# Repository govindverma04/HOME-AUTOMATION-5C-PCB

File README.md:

# HOME-AUTOMATION-5C-PCB

# Smart Home Automation PCB

This is an open-source ESP32-based smart home automation PCB designed by me.  
It includes zero-cross detection, triac dimming, relay control and support for Alexa/Google integration (optional).

---

## 🚀 Features
- ESP32-based main controller  
- 4N25 Zero-Cross Detection  
- Triac-based AC dimming  
- Relay output for AC load ON/OFF  
- Indicator LEDs  
- Safe opto-isolated design  
- Can be used for fan dimming & bulb control  

---

## 🧰 Files in this Repository
- `schematics/` → Circuit diagram  
- `pcb/` → PCB design files  
- `firmware/` → ESP32 code  
- `bom/` → Part list of components  
- `images/` → PCB photos & renders  

---

## 🔧 How to Use / Instructions

### 1) Assemble the PCB
- Solder all resistors  
- Solder optocouplers (4N25, MOC3021, etc)  
- Solder triac (BT136 or chosen model)  
- Mount terminal blocks  
- Insert ESP32  

### 2) Power Requirements
- 5V input via Hi-Link / External SMPS  
- ESP32 runs at 3.3V (regulator included)

### 3) Upload the Firmware
1. Download code from `firmware/` folder  
2. Open in Arduino IDE or PlatformIO  
3. Select board → ESP32 Dev Module  
4. Upload code  
5. Open Serial Monitor → you should see boot messages  

### 4) Connecting AC Load (⚠️ Safety First!)
- Only connect AC when you are confident  
- Use proper insulation  
- Fan/Bulb should connect through triac output  
- Relay output supports ON/OFF loads  

---

## 🧪 Testing
- Connect a test load or bulb  
- Verify Zero-Cross is detected (LED should blink)  
- Check dimming using serial or app  
- Test safety circuits  

---

## 🤝 Contributing
If you want to improve this project:
- Open an issue  
- Submit a pull request  
- Suggest new features  

---

## 📜 License
This project is open-source under the MIT License.

---

## 📞 Contact
Maintainer: **Govind**  
GitHub: https://github.com/govindverma04

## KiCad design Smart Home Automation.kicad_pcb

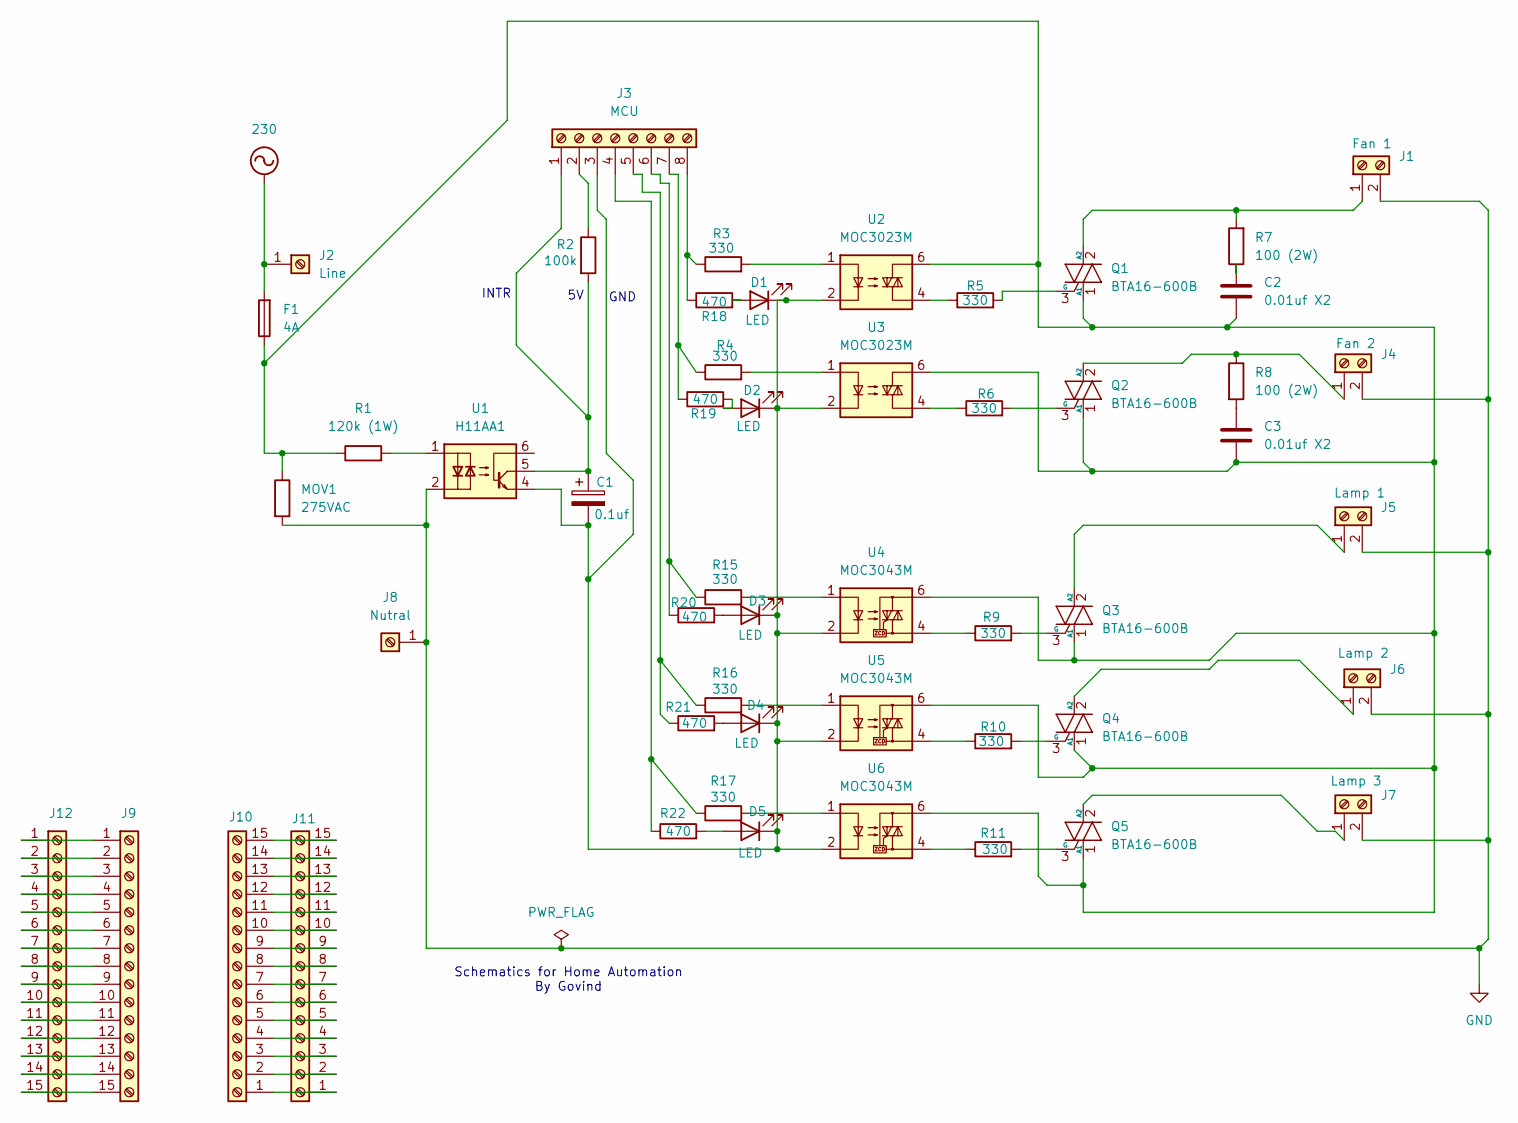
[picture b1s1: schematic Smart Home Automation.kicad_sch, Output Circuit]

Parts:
C1: 0.1uf; CP_Radial_D5.0mm_P2.00mm
C2, C3: 0.01uf X2; CP_Radial_D5.0mm_P2.00mm
D1, D2, D3, D4, D5: LED; LED_D1.8mm_W3.3mm_H2.4mm
F1: 4A; Fuseholder_Cylinder-5x20mm_Schurter_0031_8201_Horizontal_Op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
J1: Fan 1; PinSocket_1x02_P2.54mm_Vertical
J2: Line; Pin_D0.7mm_L6.5mm_W1.8mm_FlatFork
J3: MCU; PinSocket_1x08_P2.54mm_Vertical
J4: Fan 2; PinSocket_1x02_P2.54mm_Vertical
J5: Lamp 1; PinSocket_1x02_P2.54mm_Vertical
J6: Lamp 2; PinSocket_1x02_P2.54mm_Vertical
J7: Lamp 3; PinSocket_1x02_P2.54mm_Vertical
J8: Nutral; Pin_D0.7mm_L6.5mm_W1.8mm_FlatFork
J9, J10, J11, J12: Screw_Terminal_01x15; PinSocket_1x15_P2.54mm_Vertical
MOV1: 275VAC; RV_Disc_D7mm_W3.4mm_P5mm
Q1, Q2, Q3, Q4, Q5: BTA16-600B; TO-220-3_Vertical
R1: 120k (1W); R_Axial_DIN0204_L3.6mm_D1.6mm_P7.62mm_Horizontal
R2: 100k; R_Axial_DIN0204_L3.6mm_D1.6mm_P5.08mm_Horizontal
R3, R4, R5, R6, R9, R10, R11, R15, R16, R17: 330; R_Axial_DIN0204_L3.6mm_D1.6mm_P5.08mm_Horizontal
R7, R8: 100 (2W); R_Axial_DIN0204_L3.6mm_D1.6mm_P5.08mm_Horizontal
R18, R19, R20, R21, R22: 470; R_Axial_DIN0204_L3.6mm_D1.6mm_P5.08mm_Horizontal
U1: H11AA1; DIP-6_W7.62mm
U2, U3: MOC3023M; DIP-6_W10.16mm
U4, U5, U6: MOC3043M; DIP-6_W10.16mm

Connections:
230: F1.2, J2.1
GND: J1.2, J4.2, J5.2, J6.2, J7.2, J8.1, MOV1.2, U1.2
unnamed: C2.1, R7.1
unnamed: C3.1, R8.2
unnamed: D1.2 (A), R18.2
unnamed: C1.2, D1.1 (K), D2.1 (K), D3.1 (K), D4.1 (K), D5.1 (K), J3.3, U1.4, U2.2, U3.2, U4.2, U5.2, U6.2
unnamed: D2.2 (A), R19.2
unnamed: D3.2 (A), R20.2
unnamed: D4.2 (A), R21.2
unnamed: D5.2 (A), R22.2
unnamed: J1.1, Q1.2 (A2), R7.2
unnamed: C1.1, J3.1, R2.2, U1.5
unnamed: J3.2, R2.1
unnamed: J3.4, R17.1, R22.1
unnamed: J3.5, R16.1, R21.1
unnamed: J3.6, R15.1, R20.1
unnamed: J3.7, R4.1, R19.1
unnamed: J3.8, R3.1, R18.1
unnamed: J4.1, Q2.2 (A2), R8.1
unnamed: J5.1, Q3.2 (A2)
unnamed: J6.1, Q4.2 (A2)
unnamed: J7.1, Q5.2 (A2)
unnamed: J10.1, J11.1
unnamed: J10.2, J11.2
unnamed: J10.3, J11.3
unnamed: J10.4, J11.4
unnamed: J10.5, J11.5
unnamed: J10.6, J11.6
unnamed: J10.7, J11.7
unnamed: J10.8, J11.8
unnamed: J10.9, J11.9
unnamed: J10.10, J11.10
unnamed: J10.11, J11.11
unnamed: J10.12, J11.12
unnamed: J10.13, J11.13
unnamed: J10.14, J11.14
unnamed: J10.15, J11.15
unnamed: J9.1, J12.1
unnamed: J9.2, J12.2
unnamed: J9.3, J12.3
unnamed: J9.4, J12.4
unnamed: J9.5, J12.5
unnamed: J9.6, J12.6
unnamed: J9.7, J12.7
unnamed: J9.8, J12.8
unnamed: J9.9, J12.9
unnamed: J9.10, J12.10
unnamed: J9.11, J12.11
unnamed: J9.12, J12.12
unnamed: J9.13, J12.13
unnamed: J9.14, J12.14
unnamed: J9.15, J12.15
unnamed: C2.2, C3.2, F1.1, MOV1.1, Q1.1 (A1), Q2.1 (A1), Q3.1 (A1), Q4.1 (A1), Q5.1 (A1), R1.1, U2.6, U3.6, U4.6, U5.6, U6.6
unnamed: Q1.3 (G), R5.2
unnamed: Q2.3 (G), R6.2
unnamed: Q3.3 (G), R9.2
unnamed: Q4.3 (G), R10.2
unnamed: Q5.3 (G), R11.2
unnamed: R1.2, U1.1
unnamed: R3.2, U2.1
unnamed: R4.2, U3.1
unnamed: R5.1, U2.4
unnamed: R6.1, U3.4
unnamed: R9.1, U4.4
unnamed: R10.1, U5.4
unnamed: R11.1, U6.4
unnamed: R15.2, U4.1
unnamed: R16.2, U5.1
unnamed: R17.2, U6.1

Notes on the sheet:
Schematics for Home Automation By Govind
INTR
GND

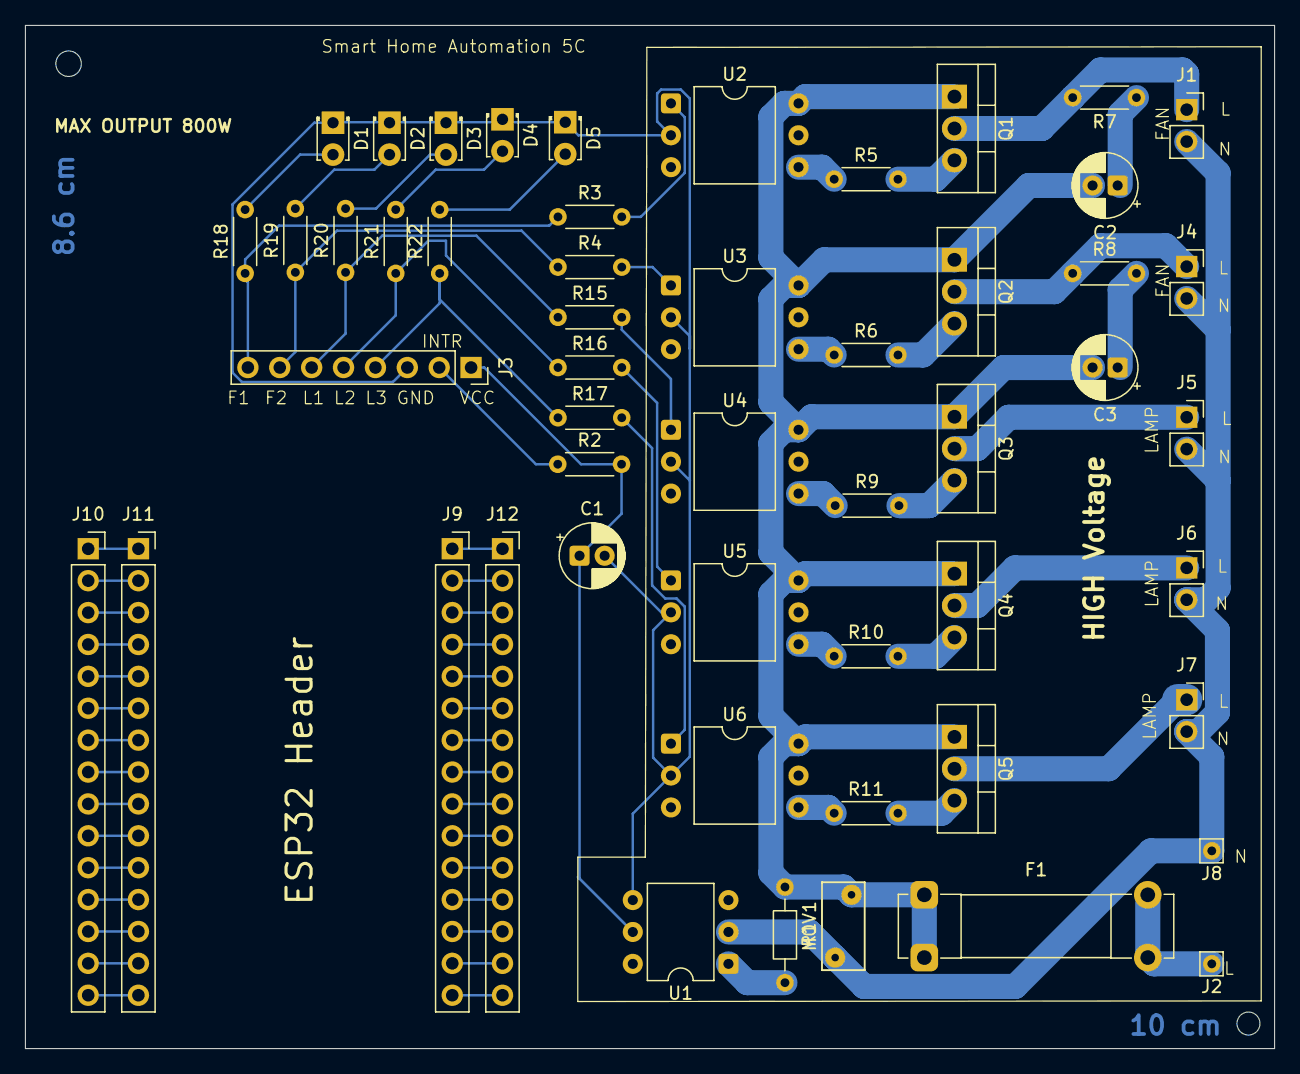
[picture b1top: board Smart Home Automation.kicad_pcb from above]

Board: 2 copper layers, 99.5 x 81.5 mm, 52 parts (0 on the bottom side), 69 nets.

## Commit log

2025-12-04 Enhance README with project details and instructions
    Added detailed project description, features, instructions, and contact information.
2025-12-04 Add 5-channel TRIAC controller firmware
    Implement a debug build for a 5-channel TRIAC controller with WiFi and SinricPro integration.
